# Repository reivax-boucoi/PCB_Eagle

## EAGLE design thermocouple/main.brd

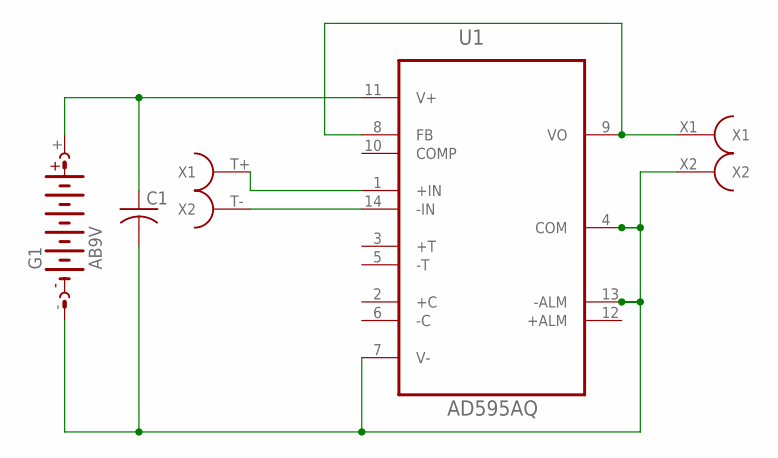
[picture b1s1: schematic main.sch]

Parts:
C1: C-USC0603; C0603
G1: AB9V
IN: THERMOCOUPLE
OUT: BANANA_19MM
U1: AD595AQ; DIP254P762X528-14P

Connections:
GND: C1.2, G1.-, OUT.X2, U1.4 (COM), U1.7 (V-), U1.13 (-ALM)
unnamed: IN.T- (X2), U1.14 (-IN)
unnamed: IN.T+ (X1), U1.1 (+IN)
OUT: OUT.X1, U1.8 (FB), U1.9 (VO)
VCC: C1.1, G1.+, U1.11 (V+)

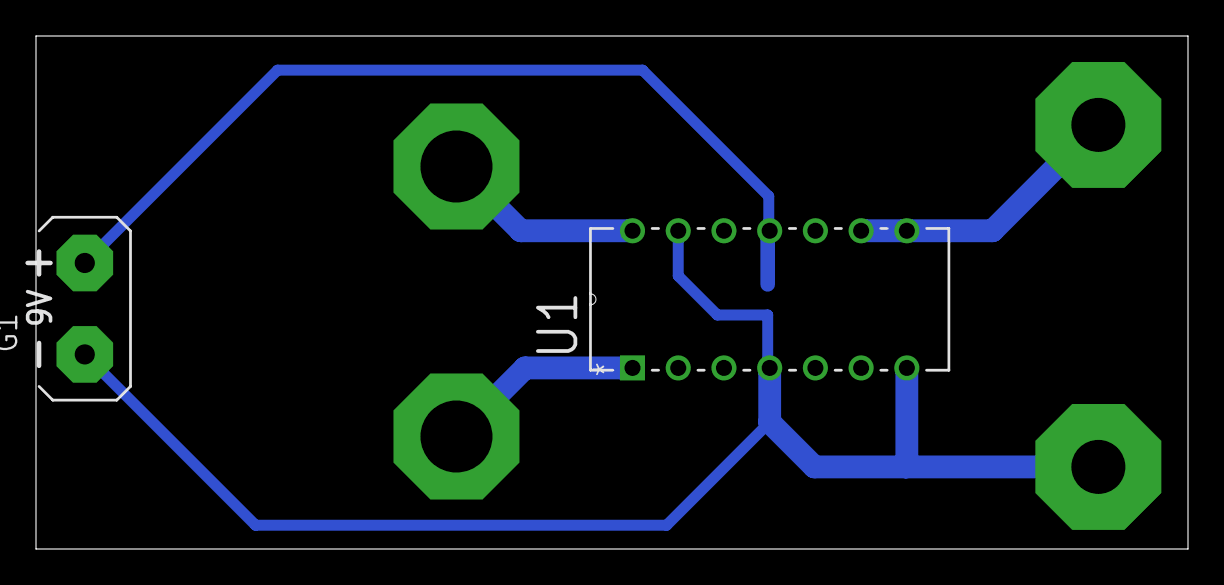
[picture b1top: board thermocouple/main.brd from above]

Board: 2 copper layers, 64.0 x 28.5 mm, 5 parts (1 on the bottom side), 5 nets.

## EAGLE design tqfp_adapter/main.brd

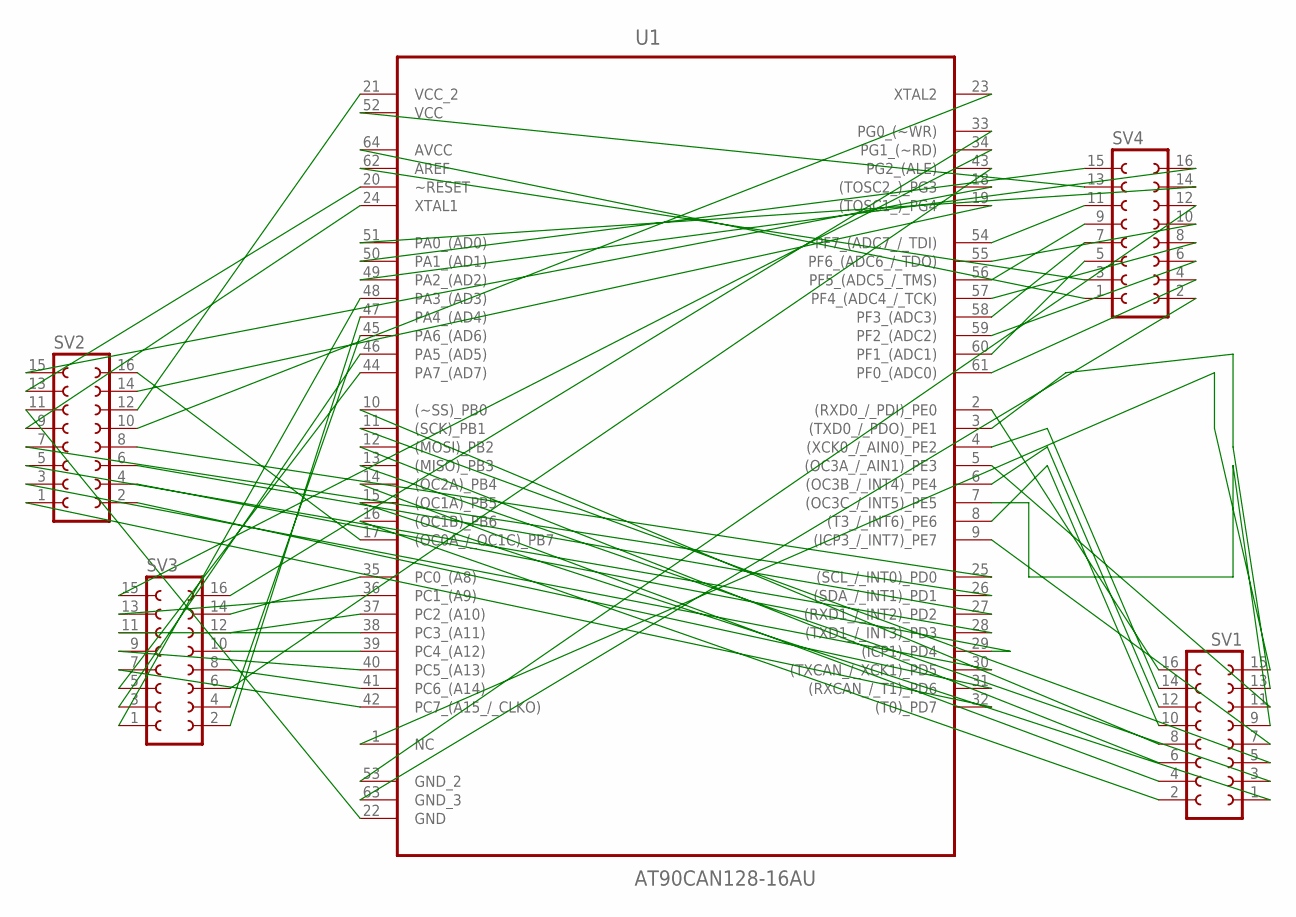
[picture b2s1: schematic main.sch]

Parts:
SV1, SV2, SV3, SV4: FE08-2
U1: AT90CAN128-16AU; QFP80P1600X1600X120-64N

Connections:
unnamed: SV4.12, U1.53 (GND_2)
unnamed: SV1.16, U1.2 ((RXD0_/_PDI)_PE0)
unnamed: SV1.14, U1.4 ((XCK0_/_AIN0)_PE2)
unnamed: SV1.12, U1.6 ((OC3B_/_INT4)_PE4)
unnamed: SV1.10, U1.8 ((T3_/_INT6)_PE6)
unnamed: SV1.15, U1.1 (NC)
unnamed: SV4.2, U1.63 (GND_3)
unnamed: SV1.9, U1.7 ((OC3C_/_INT5)_PE5)
unnamed: SV1.7, U1.9 ((ICP3_/_INT7)_PE7)
unnamed: SV1.8, U1.10 ((~SS)_PB0)
unnamed: SV1.5, U1.11 ((SCK)_PB1)
unnamed: SV1.6, U1.12 ((MOSI)_PB2)
unnamed: SV1.3, U1.13 ((MISO)_PB3)
unnamed: SV1.4, U1.14 ((OC2A)_PB4)
unnamed: SV1.1, U1.15 ((OC1A)_PB5)
unnamed: SV1.2, U1.16 ((OC1B)_PB6)
unnamed: SV2.16, U1.17 ((OC0A_/_OC1C)_PB7)
unnamed: SV2.12, U1.21 (VCC_2)
unnamed: SV2.13, U1.20 (~RESET)
unnamed: SV2.9, U1.24 (XTAL1)
unnamed: SV2.11, U1.22 (GND)
unnamed: SV2.1, U1.32 ((T0)_PD7)
unnamed: SV2.2, U1.31 ((RXCAN_/_T1)_PD6)
unnamed: SV2.3, U1.30 ((TXCAN_/_XCK1)_PD5)
unnamed: SV2.4, U1.29 ((ICP1)_PD4)
unnamed: SV2.5, U1.28 ((TXD1_/_INT3)_PD3)
unnamed: SV2.6, U1.27 ((RXD1_/_INT2)_PD2)
unnamed: SV2.7, U1.26 ((SDA_/_INT1)_PD1)
unnamed: SV2.8, U1.25 ((SCL_/_INT0)_PD0)
unnamed: SV2.10, U1.23 (XTAL2)
unnamed: SV2.15, U1.18 ((TOSC2_)_PG3)
unnamed: SV2.14, U1.19 ((TOSC1_)_PG4)
unnamed: SV3.16, U1.33 (PG0_(~WR))
unnamed: SV3.15, U1.34 (PG1_(~RD))
unnamed: SV3.14, U1.35 (PC0_(A8))
unnamed: SV3.13, U1.36 (PC1_(A9))
unnamed: SV3.12, U1.37 (PC2_(A10))
unnamed: SV3.11, U1.38 (PC3_(A11))
unnamed: SV3.10, U1.39 (PC4_(A12))
unnamed: SV3.9, U1.40 (PC5_(A13))
unnamed: SV3.8, U1.41 (PC6_(A14))
unnamed: SV3.7, U1.42 (PC7_(A15_/_CLKO))
unnamed: SV3.5, U1.44 (PA7_(AD7))
unnamed: SV3.4, U1.45 (PA6_(AD6))
unnamed: SV3.3, U1.46 (PA5_(AD5))
unnamed: SV3.2, U1.47 (PA4_(AD4))
unnamed: SV3.1, U1.48 (PA3_(AD3))
unnamed: SV3.6, U1.43 (PG2_(ALE))
unnamed: SV4.4, U1.61 (PF0_(ADC0))
unnamed: SV4.5, U1.60 (PF1_(ADC1))
unnamed: SV4.6, U1.59 (PF2_(ADC2))
unnamed: SV4.7, U1.58 (PF3_(ADC3))
unnamed: SV4.8, U1.57 (PF4_(ADC4_/_TCK))
unnamed: SV4.9, U1.56 (PF5_(ADC5_/_TMS))
unnamed: SV4.10, U1.55 (PF6_(ADC6_/_TDO))
unnamed: SV4.11, U1.54 (PF7_(ADC7_/_TDI))
unnamed: SV4.13, U1.52 (VCC)
unnamed: SV1.13, U1.3 ((TXD0_/_PDO)_PE1)
unnamed: SV4.1, U1.64 (AVCC)
unnamed: SV4.3, U1.62 (AREF)
unnamed: SV4.14, U1.51 (PA0_(AD0))
unnamed: SV4.15, U1.50 (PA1_(AD1))
unnamed: SV4.16, U1.49 (PA2_(AD2))
unnamed: SV1.11, U1.5 ((OC3A_/_AIN1)_PE3)

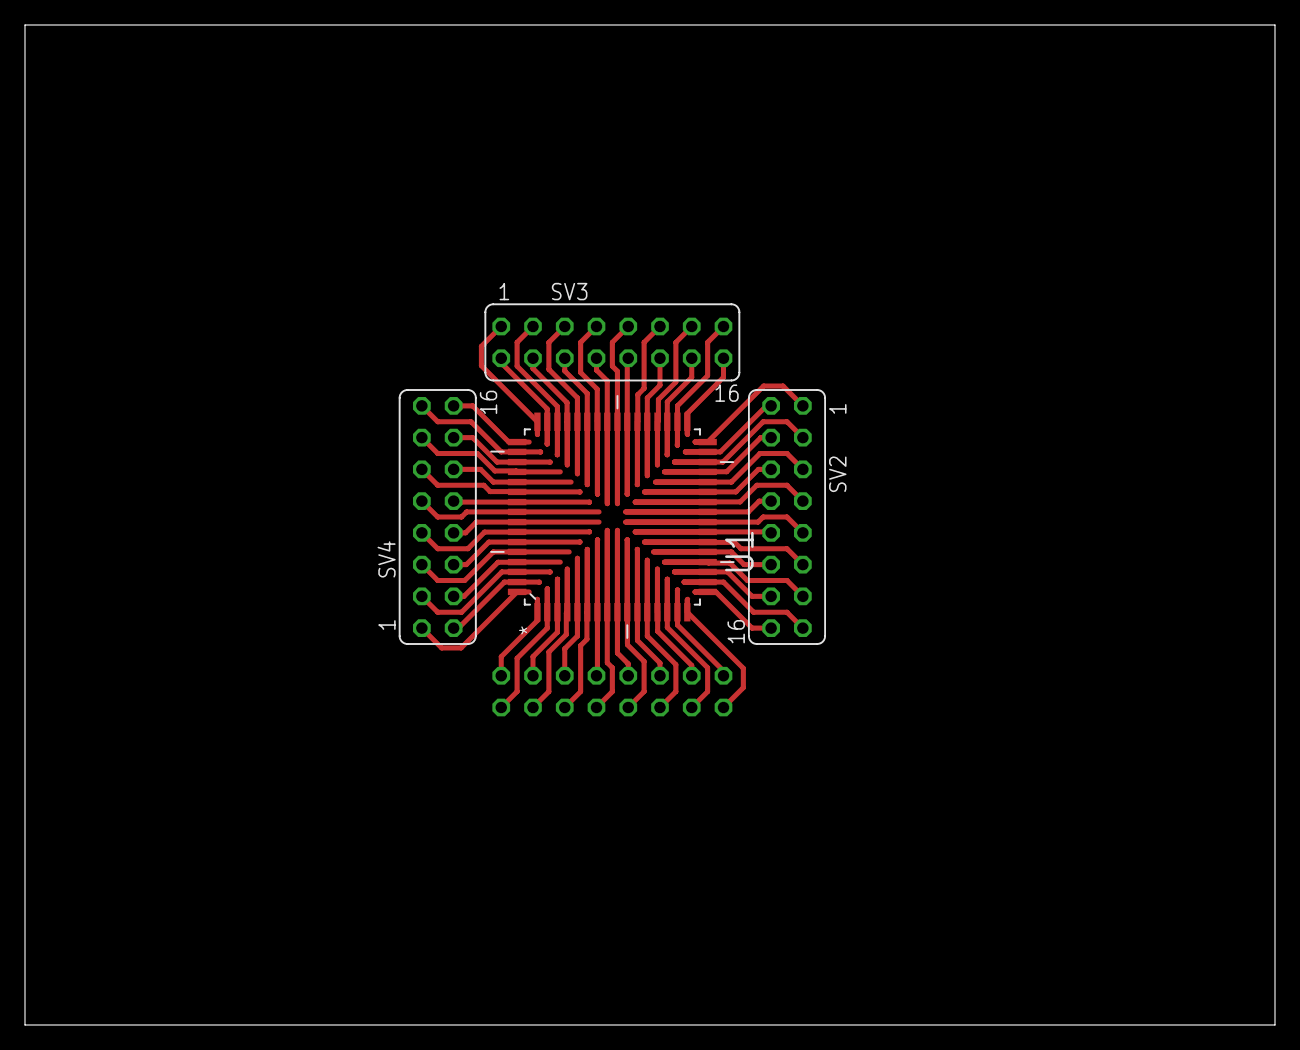
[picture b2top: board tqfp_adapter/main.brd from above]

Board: 2 copper layers, 100.0 x 80.0 mm, 5 parts (1 on the bottom side), 64 nets.

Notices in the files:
parts and their libraries:
SparkFun-Connectors: Licensing: Creative Commons ShareAlike 4.0 International - https://creativecommons.org/licenses/by-sa/4.0
